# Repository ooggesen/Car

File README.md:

# Remote Car

This project contains the PCB, code and CAD files for a small remotely controlled car. It is based uppon an Arduino Micro.

The PCB files are generated with KiCAD and can be found in the folder Platine.

The code for running the car can be found in the folder Code/Car_Backend and the controller from which to access the car is stored in Car/Car_Frontend.

The folder Body contains stl files, from which the body of the car could be build

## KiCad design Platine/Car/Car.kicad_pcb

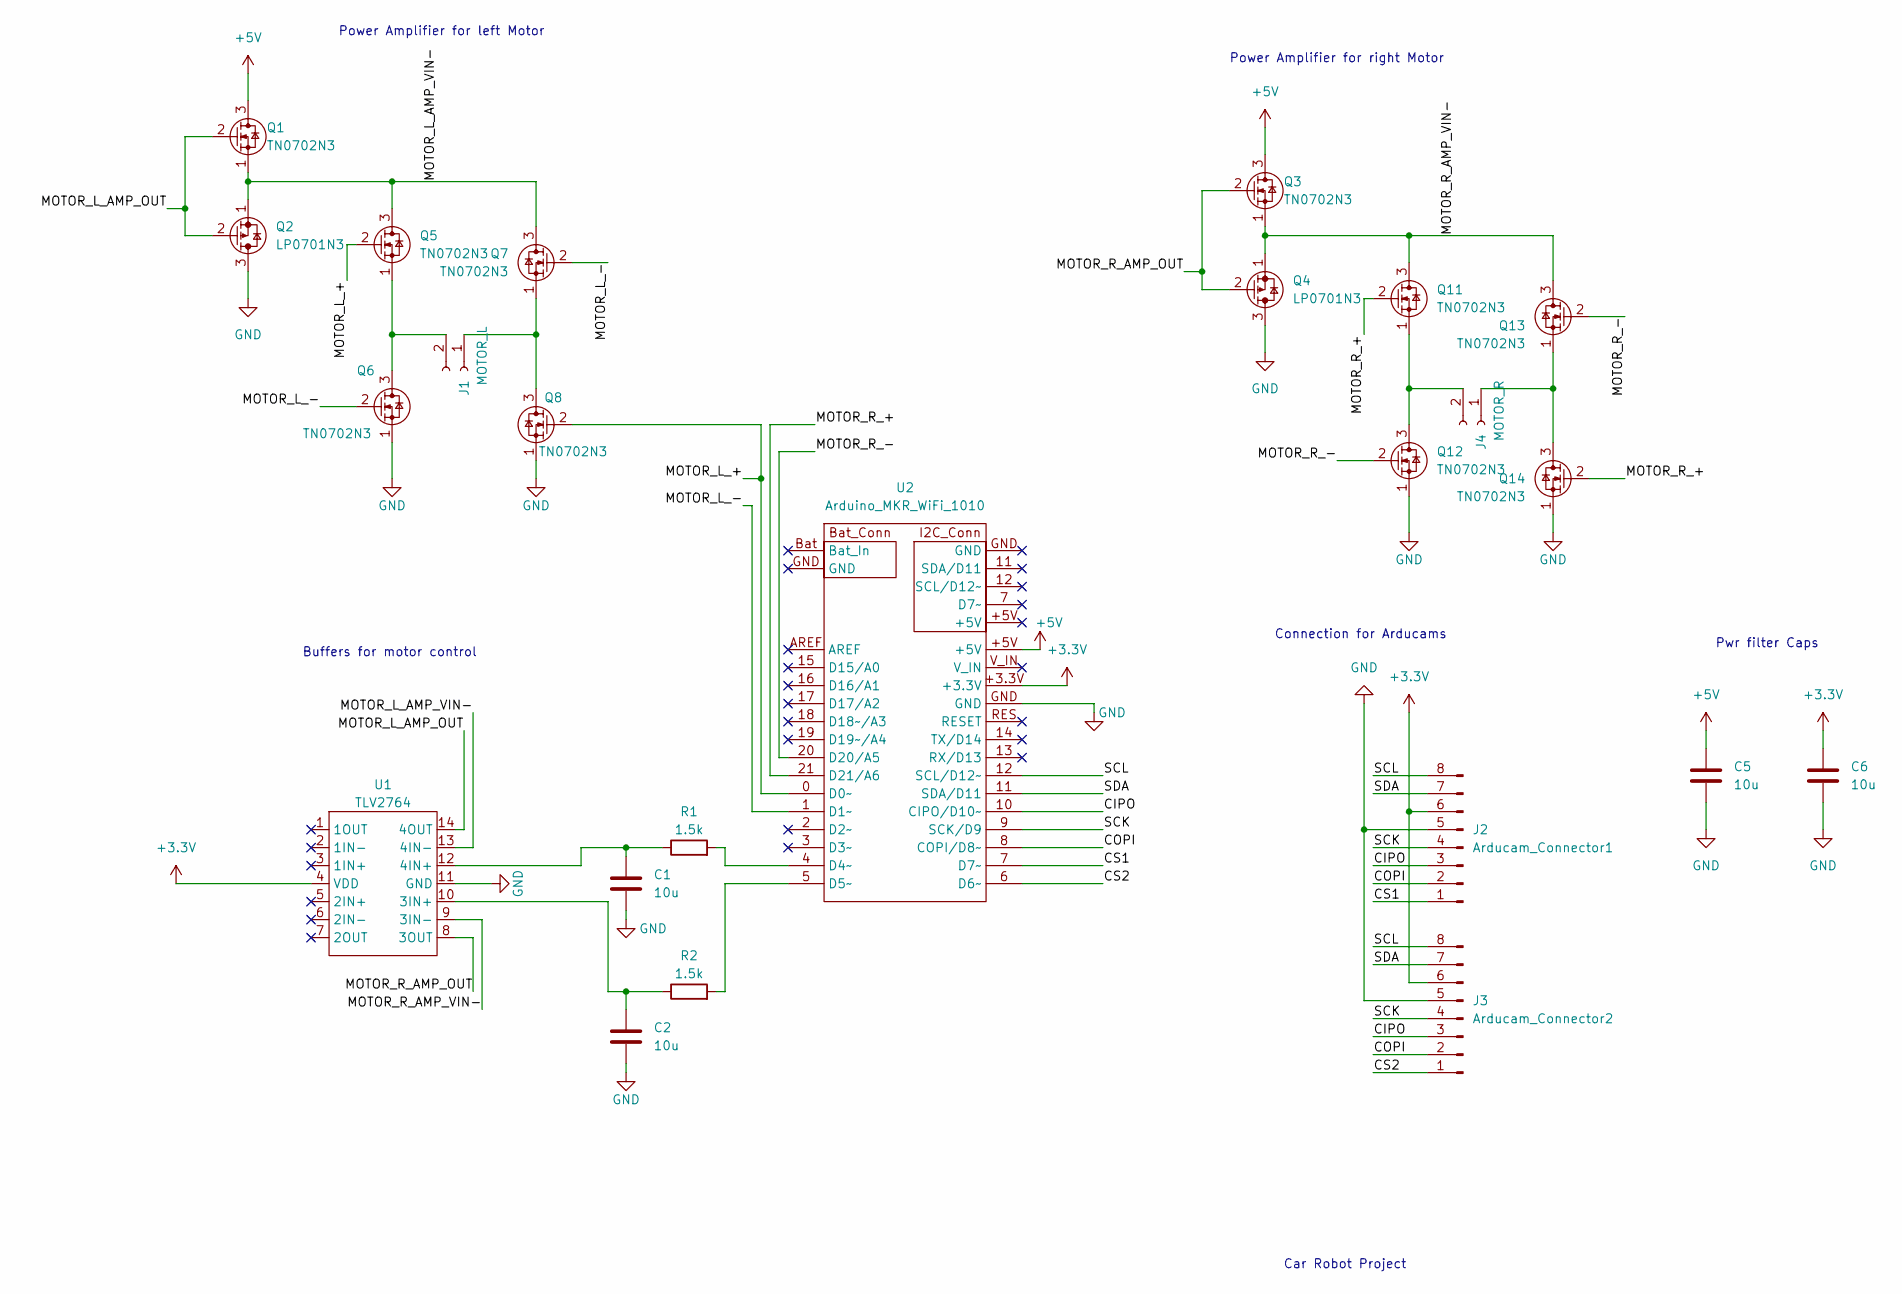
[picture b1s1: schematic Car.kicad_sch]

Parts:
C1, C2, C5, C6: 10u; CP_Radial_D5.0mm_P2.50mm
J1: MOTOR_L; PinHeader_1x02_P2.00mm_Vertical
J2: Arducam_Connector1; PinHeader_1x08_P2.54mm_Vertical
J3: Arducam_Connector2; PinHeader_1x08_P2.54mm_Vertical
J4: MOTOR_R; PinHeader_1x02_P2.00mm_Vertical
Q1, Q3, Q5, Q6, Q7, Q8, Q11, Q12, Q13, Q14: TN0702N3; TO-92L_Inline
Q2, Q4: LP0701N3; TO-92L_Inline
R1, R2: 1.5k; R_Axial_DIN0207_L6.3mm_D2.5mm_P10.16mm_Horizontal
U1: TLV2764; DIP-14_W7.62mm
U2: Arduino_MKR_WiFi_1010; Arduino_MKR_1010

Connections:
+3V3: C6.1, J2.6, J3.6, U1.4 (VDD), U2.+3.3V
+5V: C5.1, Q1.3, Q3.3, U2.+5V
/CIPO: J2.3, J3.3, U2.10 (CIPO/D10~)
/COPI: J2.2, J3.2, U2.8 (COPI/D8~)
/CS1: J2.1, U2.7 (D7~)
/CS2: J3.1, U2.6 (D6~)
/MOTOR_L_+: Q5.2, Q8.2, U2.0 (D0~)
/MOTOR_L_-: Q6.2, Q7.2, U2.1 (D1~)
/MOTOR_L_AMP_OUT: Q1.2, Q2.2, U1.14 (4OUT)
/MOTOR_L_AMP_VIN-: Q1.1, Q2.1, Q5.3, Q7.3, U1.13 (4IN-)
/MOTOR_R_+: Q11.2, Q14.2, U2.21 (D21/A6)
/MOTOR_R_-: Q12.2, Q13.2, U2.20 (D20/A5)
/MOTOR_R_AMP_OUT: Q3.2, Q4.2, U1.8 (3OUT)
/MOTOR_R_AMP_VIN-: Q3.1, Q4.1, Q11.3, Q13.3, U1.9 (3IN-)
/SCK: J2.4, J3.4, U2.9 (SCK/D9)
/SCL: J2.8, J3.8, U2.12 (SCL/D12~)
/SDA: J2.7, J3.7, U2.11 (SDA/D11)
GND: C1.2, C2.2, C5.2, C6.2, J2.5, J3.5, Q2.3, Q4.3, Q6.1, Q8.1, Q12.1, Q14.1, U1.11 (GND), U2.GND
unnamed: C1.1, R1.1, U1.12 (4IN+)
unnamed: C2.1, R2.1, U1.10 (3IN+)
unnamed: J1.1, Q7.1, Q8.3
unnamed: J1.2, Q5.1, Q6.3
unnamed: J4.1, Q13.1, Q14.3
unnamed: J4.2, Q11.1, Q12.3
unnamed: R1.2, U2.4 (D4~)
unnamed: R2.2, U2.5 (D5~)

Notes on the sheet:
Pwr filter Caps
Power Amplifier for right Motor
Buffers for motor control
Connection for Arducams
Car Robot Project
Power Amplifier for left Motor

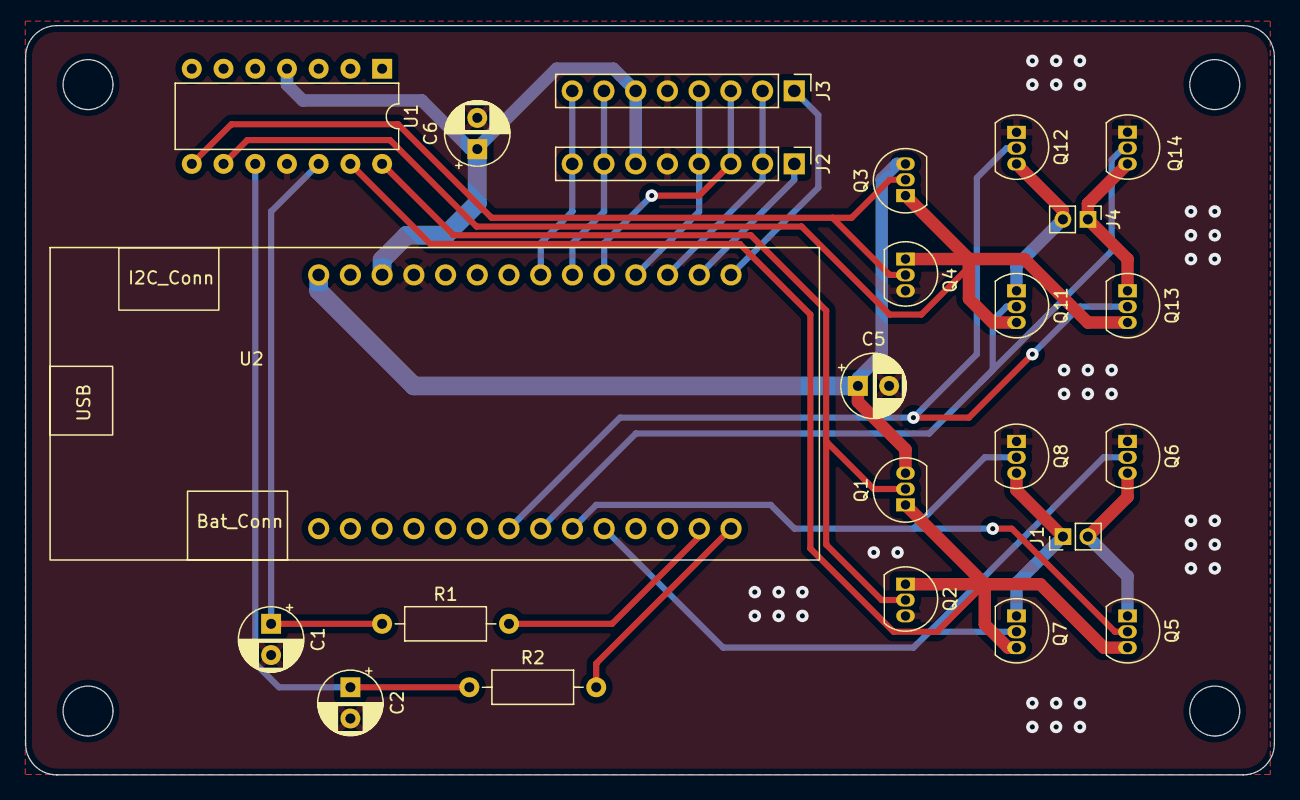
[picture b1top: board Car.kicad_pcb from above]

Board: 2 copper layers, 100.0 x 60.0 mm, 24 parts (0 on the bottom side), 26 nets.

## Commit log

2022-08-31 Initial commit. Software running motors and wifi connection testet. Hardware support for motors tested.
2022-10-17 Car software tested for motor control and camera capture. Success
2022-10-21 Backend implemented protthreads, for sending images and wifi server.
2022-10-28 Sending and receiving of photo tested. With addtional conditions in Server backend, which check the beginning and ending of a jpeg frame.
2022-10-29 Changed reception of messages to bytesarray, with recognition of the end of the jpg frame. All image qualities work now.
2022-12-20 Refactoring the backend code
2022-12-21 Small changes and refactoring of car frontend
2023-01-08 Refactoring and small changes
2023-03-18 First verion on pcb tested and functional.
2023-11-13 Small change in gitignore
2023-11-13 Removed DS Store data
2023-11-13 Removed pychache
2023-11-13 Removal of __pycache__
2023-11-13 added simple READEME
